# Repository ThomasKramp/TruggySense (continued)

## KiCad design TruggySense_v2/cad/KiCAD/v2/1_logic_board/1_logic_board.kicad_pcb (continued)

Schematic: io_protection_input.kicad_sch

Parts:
D4: TVS_SMF3.3; Nexperia_DSN1608-2_1.6x0.8mm
F1: SMD0805B010TF; Fuse_0805_2012Metric_Pad1.15x1.40mm_HandSolder

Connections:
/ADC/IO_Protection/ADC Buffer 1/IN_1: D4.1 (K), F1.2; also elsewhere on the board
/ADC/IO_Protection/IN_1: F1.1; also elsewhere on the board
GND: D4.2 (A); also elsewhere on the board

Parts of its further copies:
D5, D6, D7, D8, D9, D10, D11, D12, D13, D19, D20, D21, D22, D23, D24, D25, D26, D27, D28, D29, D30, D31, D32, D33, D34, D35: TVS_SMF3.3; Nexperia_DSN1608-2_1.6x0.8mm
F2, F3, F4, F5, F6, F7, F8, F9, F10, F16, F17, F18, F19, F20, F21, F22, F23, F24, F25, F26, F27, F28, F29, F30, F31, F32: SMD0805B010TF; Fuse_0805_2012Metric_Pad1.15x1.40mm_HandSolder

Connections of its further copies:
/ADC/IO_Protection/ADC Buffer 1/IN_2: D5.1 (K), F2.2; also elsewhere on the board
/ADC/IO_Protection/ADC Buffer 2/IN_1: D6.1 (K), F3.2; also elsewhere on the board
/ADC/IO_Protection/ADC Buffer 2/IN_2: D7.1 (K), F4.2; also elsewhere on the board
/ADC/IO_Protection/ADC Buffer 3/IN_1: D8.1 (K), F5.2; also elsewhere on the board
/ADC/IO_Protection/ADC Buffer 3/IN_2: D9.1 (K), F6.2; also elsewhere on the board
/ADC/IO_Protection/ADC Buffer 4/IN_1: D10.1 (K), F7.2; also elsewhere on the board
/ADC/IO_Protection/ADC Buffer 4/IN_2: D11.1 (K), F8.2; also elsewhere on the board
/ADC/IO_Protection/ADC Buffer 5/IN_1: D12.1 (K), F9.2; also elsewhere on the board
/ADC/IO_Protection/ADC Buffer 5/IN_2: D13.1 (K), F10.2; also elsewhere on the board
/ADC/IO_Protection/IN_2: F2.1; also elsewhere on the board
/ADC/IO_Protection/IN_3: F3.1; also elsewhere on the board
/ADC/IO_Protection/IN_4: F4.1; also elsewhere on the board
/ADC/IO_Protection/IN_5: F5.1; also elsewhere on the board
/ADC/IO_Protection/IN_6: F6.1; also elsewhere on the board
/ADC/IO_Protection/IN_7: F7.1; also elsewhere on the board
/ADC/IO_Protection/IN_8: F8.1; also elsewhere on the board
/ADC/IO_Protection/IN_9: F9.1; also elsewhere on the board
/ADC/IO_Protection/IN_10: F10.1; also elsewhere on the board
/SPI/IO_Protection/IN_1: F18.1; also elsewhere on the board
/SPI/IO_Protection/IN_2: F19.1; also elsewhere on the board
/SPI/IO_Protection/IN_3: F20.1; also elsewhere on the board
/SPI/IO_Protection/IN_4: F21.1; also elsewhere on the board
/SPI/IO_Protection/IN_5: F22.1; also elsewhere on the board
/UART/IO_Protection/IN_1: F23.1; also elsewhere on the board
/UART/IO_Protection/IN_2: F24.1; also elsewhere on the board
/UART/IO_Protection/IN_3: F25.1; also elsewhere on the board
/UART/IO_Protection/IN_4: F26.1; also elsewhere on the board
/UART/IO_Protection/IN_5: F27.1; also elsewhere on the board
/UART/IO_Protection/IN_6: F28.1; also elsewhere on the board
/UART/IO_Protection/Input Protection 2/OUT: D27.1 (K), F24.2; also elsewhere on the board
/UART/IO_Protection/Input Protection 6/OUT: D31.1 (K), F28.2; also elsewhere on the board
/Various Inputs/IO_Protection/IN_1: F29.1; also elsewhere on the board
/Various Inputs/IO_Protection/IN_2: F30.1; also elsewhere on the board
/Various Inputs/IO_Protection/IN_3: F31.1; also elsewhere on the board
/Various Inputs/IO_Protection/IN_4: F32.1; also elsewhere on the board
GND: D5.2 (A), D6.2 (A), D7.2 (A), D8.2 (A), D9.2 (A), D10.2 (A), D11.2 (A), D12.2 (A), D13.2 (A), D19.2 (A), D20.2 (A), D21.2 (A), D22.2 (A), D23.2 (A), D24.2 (A), D25.2 (A), D26.2 (A), D27.2 (A), D28.2 (A), D29.2 (A), D30.2 (A), D31.2 (A), D32.2 (A), D33.2 (A), D34.2 (A), D35.2 (A); also elsewhere on the board
GPS_SCL: F17.1; also elsewhere on the board
GPS_SDA: F16.1; also elsewhere on the board
HALL_W_FL: D33.1 (K), F30.2; also elsewhere on the board
HALL_W_FR: D32.1 (K), F29.2; also elsewhere on the board
HALL_W_RL: D35.1 (K), F32.2; also elsewhere on the board
HALL_W_RR: D34.1 (K), F31.2; also elsewhere on the board
I2C_SCL: D20.1 (K), F17.2; also elsewhere on the board
I2C_SDA: D19.1 (K), F16.2; also elsewhere on the board
SPI_CE: D25.1 (K), F22.2; also elsewhere on the board
SPI_CS: D22.1 (K), F19.2; also elsewhere on the board
SPI_MISO: D24.1 (K), F21.2; also elsewhere on the board
SPI_MOSI: D23.1 (K), F20.2; also elsewhere on the board
SPI_SCK: D21.1 (K), F18.2; also elsewhere on the board
UART_GPS_RX: D28.1 (K), F25.2; also elsewhere on the board
UART_GPS_TX: D29.1 (K), F26.2; also elsewhere on the board
UART_IBUS_RX: D26.1 (K), F23.2; also elsewhere on the board
UART_USB_RX: D30.1 (K), F27.2; also elsewhere on the board

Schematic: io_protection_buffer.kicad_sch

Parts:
C86: 100nF; C_0805_2012Metric_Pad1.18x1.45mm_HandSolder
C87: 1µF; C_0805_2012Metric_Pad1.18x1.45mm_HandSolder
R73, R74, R75, R76: 10; R_0805_2012Metric_Pad1.20x1.40mm_HandSolder
U8: OPA2890ID; SOIC-8_3.9x4.9mm_P1.27mm

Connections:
+3V3: C86.1, C87.1, U8.8 (V+); also elsewhere on the board
/ADC/IO_Protection/ADC Buffer 1/IN_1: R73.1; also elsewhere on the board
/ADC/IO_Protection/ADC Buffer 1/IN_2: R75.1; also elsewhere on the board
ADC_V_B_C1: R74.2; also elsewhere on the board
ADC_V_B_C2: R76.2; also elsewhere on the board
GND: C86.2, C87.2, U8.4 (V-); also elsewhere on the board
unnamed: R73.2, U8.3 (+)
unnamed: R74.1, U8.1, U8.2 (-)
unnamed: R75.2, U8.5 (+)
unnamed: R76.1, U8.6 (-), U8.7

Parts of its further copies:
C88, C90, C92, C94, C96, C98: 100nF; C_0805_2012Metric_Pad1.18x1.45mm_HandSolder
C89, C91, C93, C95, C97, C99: 1µF; C_0805_2012Metric_Pad1.18x1.45mm_HandSolder
R77, R78, R79, R80, R81, R82, R83, R84, R85, R86, R87, R88, R89, R90, R91, R92, R108, R109, R110, R111, R112, R113, R114, R115: 10; R_0805_2012Metric_Pad1.20x1.40mm_HandSolder
U9, U10, U11, U12, U18, U19: OPA2890ID; SOIC-8_3.9x4.9mm_P1.27mm

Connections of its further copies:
+3V3: C88.1, C89.1, C90.1, C91.1, C92.1, C93.1, C94.1, C95.1, C96.1, C97.1, C98.1, C99.1, U9.8 (V+), U10.8 (V+), U11.8 (V+), U12.8 (V+), U18.8 (V+), U19.8 (V+); also elsewhere on the board
/ADC/IO_Protection/ADC Buffer 2/IN_1: R77.1; also elsewhere on the board
/ADC/IO_Protection/ADC Buffer 2/IN_2: R79.1; also elsewhere on the board
/ADC/IO_Protection/ADC Buffer 3/IN_1: R81.1; also elsewhere on the board
/ADC/IO_Protection/ADC Buffer 3/IN_2: R83.1; also elsewhere on the board
/ADC/IO_Protection/ADC Buffer 4/IN_1: R85.1; also elsewhere on the board
/ADC/IO_Protection/ADC Buffer 4/IN_2: R87.1; also elsewhere on the board
/ADC/IO_Protection/ADC Buffer 5/IN_1: R89.1; also elsewhere on the board
/ADC/IO_Protection/ADC Buffer 5/IN_2: R91.1; also elsewhere on the board
/UART/IO_Protection/Input Protection 2/OUT: R108.1; also elsewhere on the board
/UART/IO_Protection/Input Protection 6/OUT: R112.1; also elsewhere on the board
/UART/IO_Protection/UART Buffer 1/IN_2: R110.1
/UART/IO_Protection/UART Buffer 1/OUT_2: R111.2
/UART/IO_Protection/UART Buffer 2/IN_2: R114.1
/UART/IO_Protection/UART Buffer 2/OUT_2: R115.2
ADC_I_M_FL: R88.2; also elsewhere on the board
ADC_I_M_FR: R86.2; also elsewhere on the board
ADC_I_M_RL: R92.2; also elsewhere on the board
ADC_I_M_RR: R90.2; also elsewhere on the board
ADC_V_3.3: R82.2; also elsewhere on the board
ADC_V_5.0: R84.2; also elsewhere on the board
ADC_V_B_C3: R78.2; also elsewhere on the board
ADC_V_B_C4: R80.2; also elsewhere on the board
GND: C88.2, C89.2, C90.2, C91.2, C92.2, C93.2, C94.2, C95.2, C96.2, C97.2, C98.2, C99.2, U9.4 (V-), U10.4 (V-), U11.4 (V-), U12.4 (V-), U18.4 (V-), U19.4 (V-); also elsewhere on the board
unnamed: R77.2, U9.3 (+)
unnamed: R78.1, U9.1, U9.2 (-)
unnamed: R79.2, U9.5 (+)
unnamed: R80.1, U9.6 (-), U9.7
unnamed: R81.2, U10.3 (+)
unnamed: R82.1, U10.1, U10.2 (-)
unnamed: R83.2, U10.5 (+)
unnamed: R84.1, U10.6 (-), U10.7
unnamed: R85.2, U11.3 (+)
unnamed: R86.1, U11.1, U11.2 (-)
unnamed: R87.2, U11.5 (+)
unnamed: R88.1, U11.6 (-), U11.7
unnamed: R89.2, U12.3 (+)
unnamed: R90.1, U12.1, U12.2 (-)
unnamed: R91.2, U12.5 (+)
unnamed: R92.1, U12.6 (-), U12.7
unnamed: R108.2, U18.3 (+)
unnamed: R109.1, U18.1, U18.2 (-)
unnamed: R110.2, U18.5 (+)
unnamed: R111.1, U18.6 (-), U18.7
unnamed: R112.2, U19.3 (+)
unnamed: R113.1, U19.1, U19.2 (-)
unnamed: R114.2, U19.5 (+)
unnamed: R115.1, U19.6 (-), U19.7
UART_IBUS_TX: R109.2; also elsewhere on the board
UART_USB_TX: R113.2; also elsewhere on the board

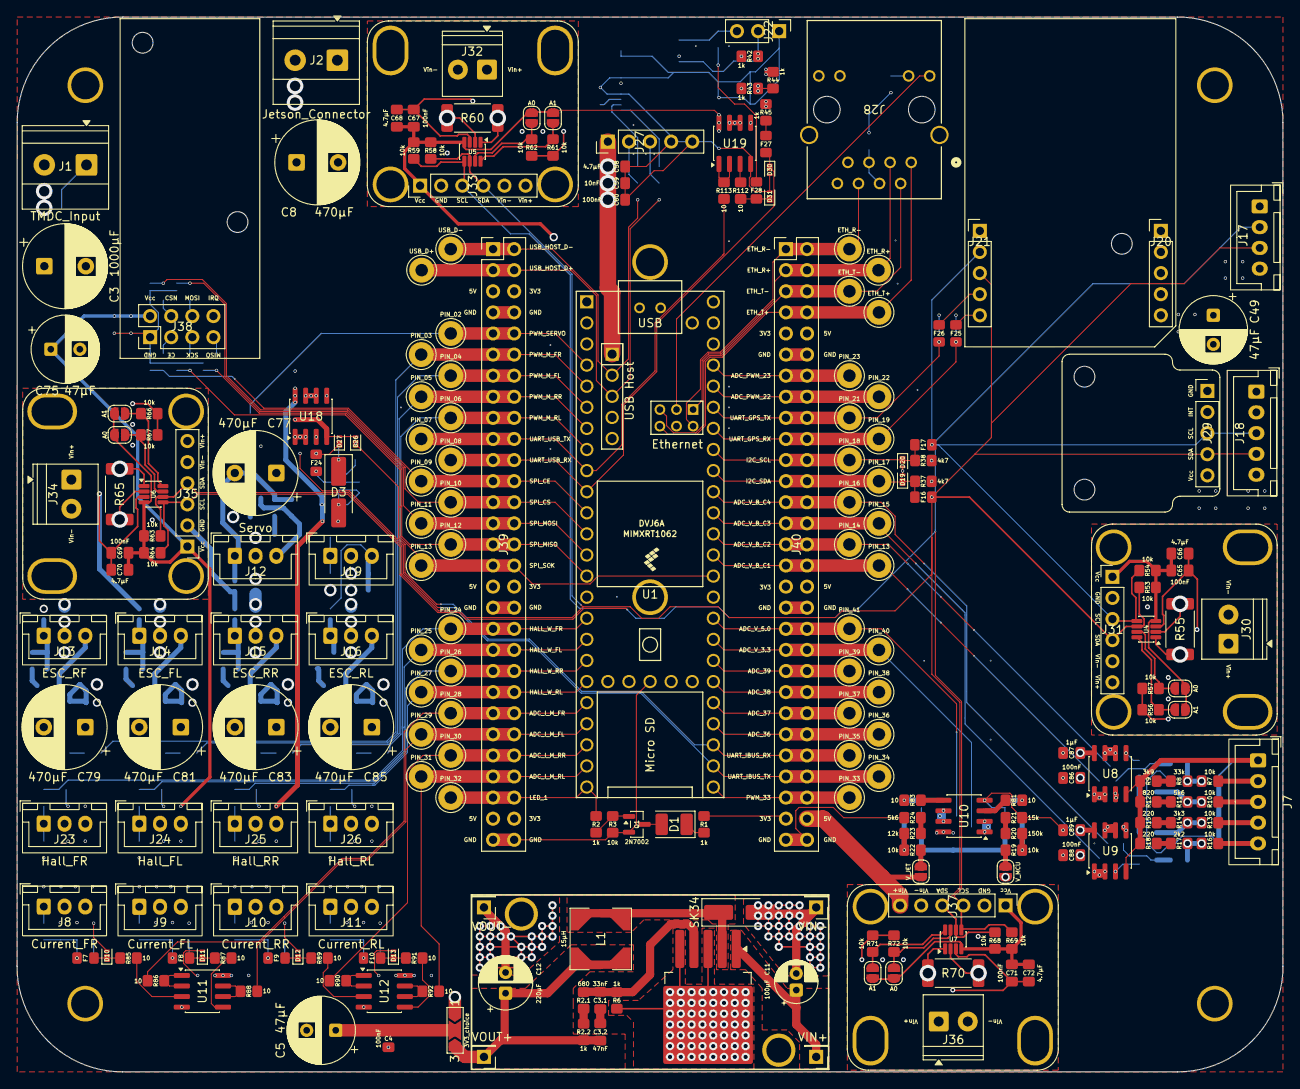
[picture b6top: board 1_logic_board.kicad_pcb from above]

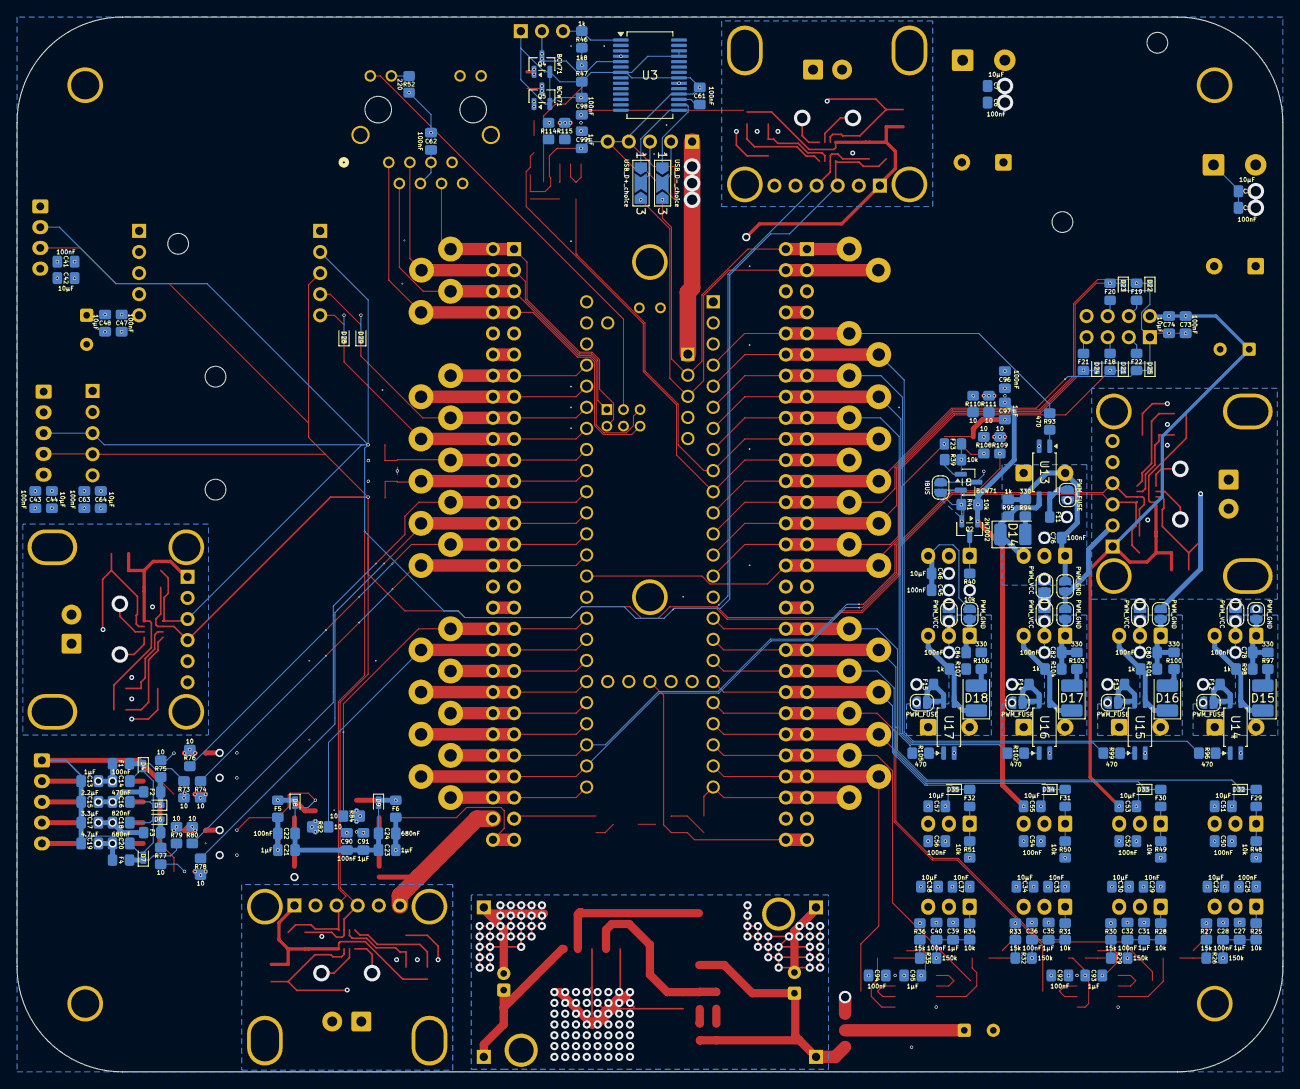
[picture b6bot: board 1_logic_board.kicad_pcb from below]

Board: 4 copper layers, 152.4 x 127.0 mm, 421 parts (193 on the bottom side), 204 nets.

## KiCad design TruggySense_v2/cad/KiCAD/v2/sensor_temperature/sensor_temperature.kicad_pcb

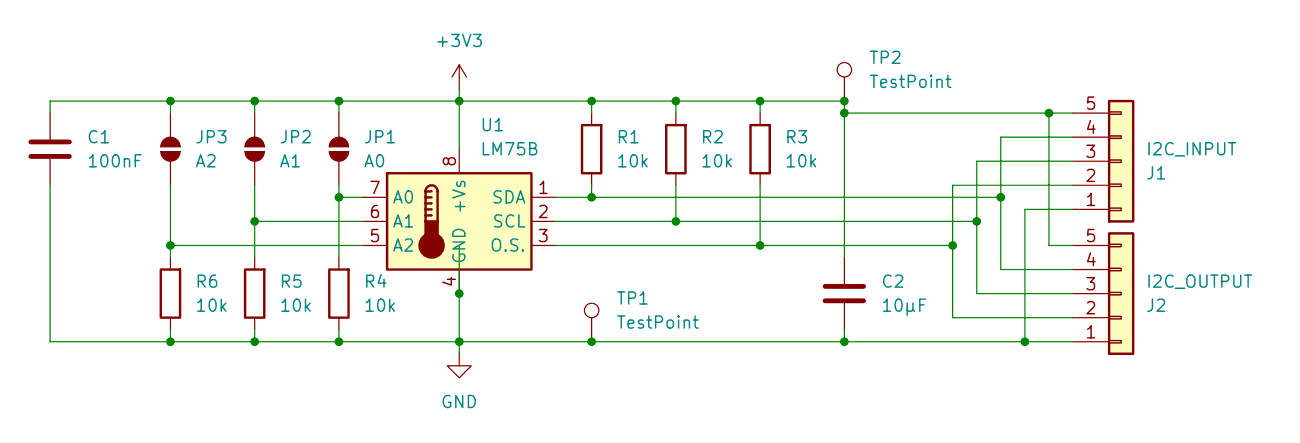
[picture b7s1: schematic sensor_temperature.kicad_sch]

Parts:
C1: 100nF; C_0805_2012Metric_Pad1.18x1.45mm_HandSolder
C2: 10µF; C_0805_2012Metric_Pad1.18x1.45mm_HandSolder
J1: I2C_INPUT; JST_XH_B5B-XH-A_1x05_P2.50mm_Vertical
J2: I2C_OUTPUT; JST_XH_B5B-XH-A_1x05_P2.50mm_Vertical
JP1: A0; SolderJumper-2_P1.3mm_Open_TrianglePad1.0x1.5mm
JP2: A1; SolderJumper-2_P1.3mm_Open_TrianglePad1.0x1.5mm
JP3: A2; SolderJumper-2_P1.3mm_Open_TrianglePad1.0x1.5mm
R1, R2, R3, R4, R5, R6: 10k; R_0805_2012Metric_Pad1.20x1.40mm_HandSolder
TP1, TP2: TestPoint; TestPoint_Pad_D1.0mm
U1: LM75B; SOIC-8_3.9x4.9mm_P1.27mm

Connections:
+3V3: C1.2, C2.2, J1.5, J2.5, JP1.2 (B), JP2.2 (B), JP3.2 (B), R1.2, R2.2, R3.2, TP2.1, U1.8 (+Vs)
GND: C1.1, C2.1, J1.1, J2.1, R4.1, R5.1, R6.1, TP1.1, U1.4 (GND)
unnamed: J1.2, J2.2, R3.1, U1.3 (O.S.)
unnamed: J1.3, J2.3, R2.1, U1.2 (SCL)
unnamed: J1.4, J2.4, R1.1, U1.1 (SDA)
unnamed: JP1.1 (A), R4.2, U1.7 (A0)
unnamed: JP2.1 (A), R5.2, U1.6 (A1)
unnamed: JP3.1 (A), R6.2, U1.5 (A2)

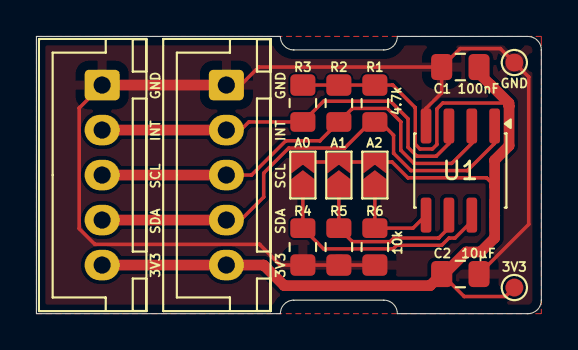
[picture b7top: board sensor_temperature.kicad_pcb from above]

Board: 2 copper layers, 28.1 x 15.4 mm, 16 parts (0 on the bottom side), 8 nets.

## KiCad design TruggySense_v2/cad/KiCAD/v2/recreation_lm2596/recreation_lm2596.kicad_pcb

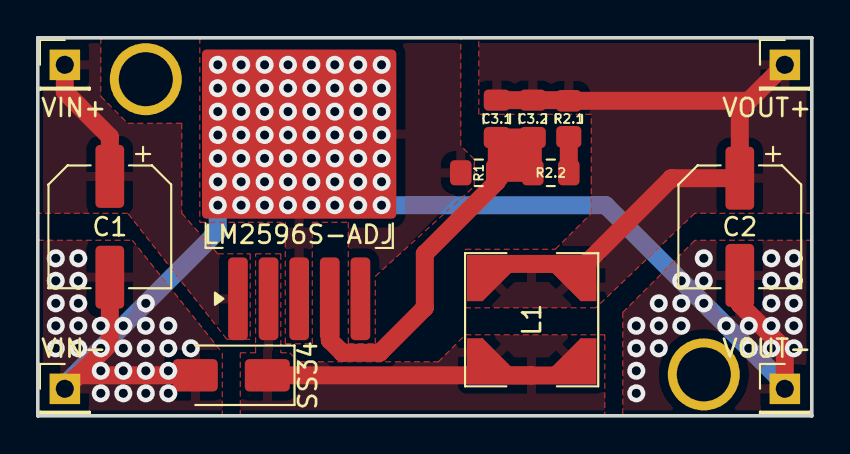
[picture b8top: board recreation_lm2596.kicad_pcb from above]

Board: 2 copper layers, 43.0 x 21.0 mm, 14 parts (0 on the bottom side), 6 nets.

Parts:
C1: 100µF/16V; CP_Elec_6.3x5.4
C2: 220µF/16V; CP_Elec_6.3x7.7
C3.1: 18nF; C_0805_2012Metric_Pad1.18x1.45mm_HandSolder
C3.2: 1.2nF; C_0805_2012Metric_Pad1.18x1.45mm_HandSolder
D1: SS34; D_SMA
J1: VIN+; PinHeader_1x01_P2.54mm_Vertical
J2: VIN-; PinHeader_1x01_P2.54mm_Vertical
J3: VOUT+; PinHeader_1x01_P2.54mm_Vertical
J4: VOUT-; PinHeader_1x01_P2.54mm_Vertical
L1: 15µH; 29153C
R1, R2.1: 1k; R_0805_2012Metric_Pad1.20x1.40mm_HandSolder
R2.2: k68; R_0805_2012Metric_Pad1.20x1.40mm_HandSolder
U1: LM2596S-ADJ; TO-263-5_TabPin3

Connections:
/V_IN+: C1.1, J1.1, U1.1 (VIN)
/V_IN-: C1.2, C2.2, D1.2 (A), J2.1, J4.1, R1.1, U1.3 (GND)
/V_OUT+: C2.1, C3.1.2, C3.2.2, J3.1, L1.2, R2.1.1
unnamed: D1.1 (K), L1.1, U1.2 (OUT)
unnamed: R2.1.2, R2.2.1
unnamed: C3.1.1, C3.2.1, R1.2, R2.2.2, U1.4 (FB)
